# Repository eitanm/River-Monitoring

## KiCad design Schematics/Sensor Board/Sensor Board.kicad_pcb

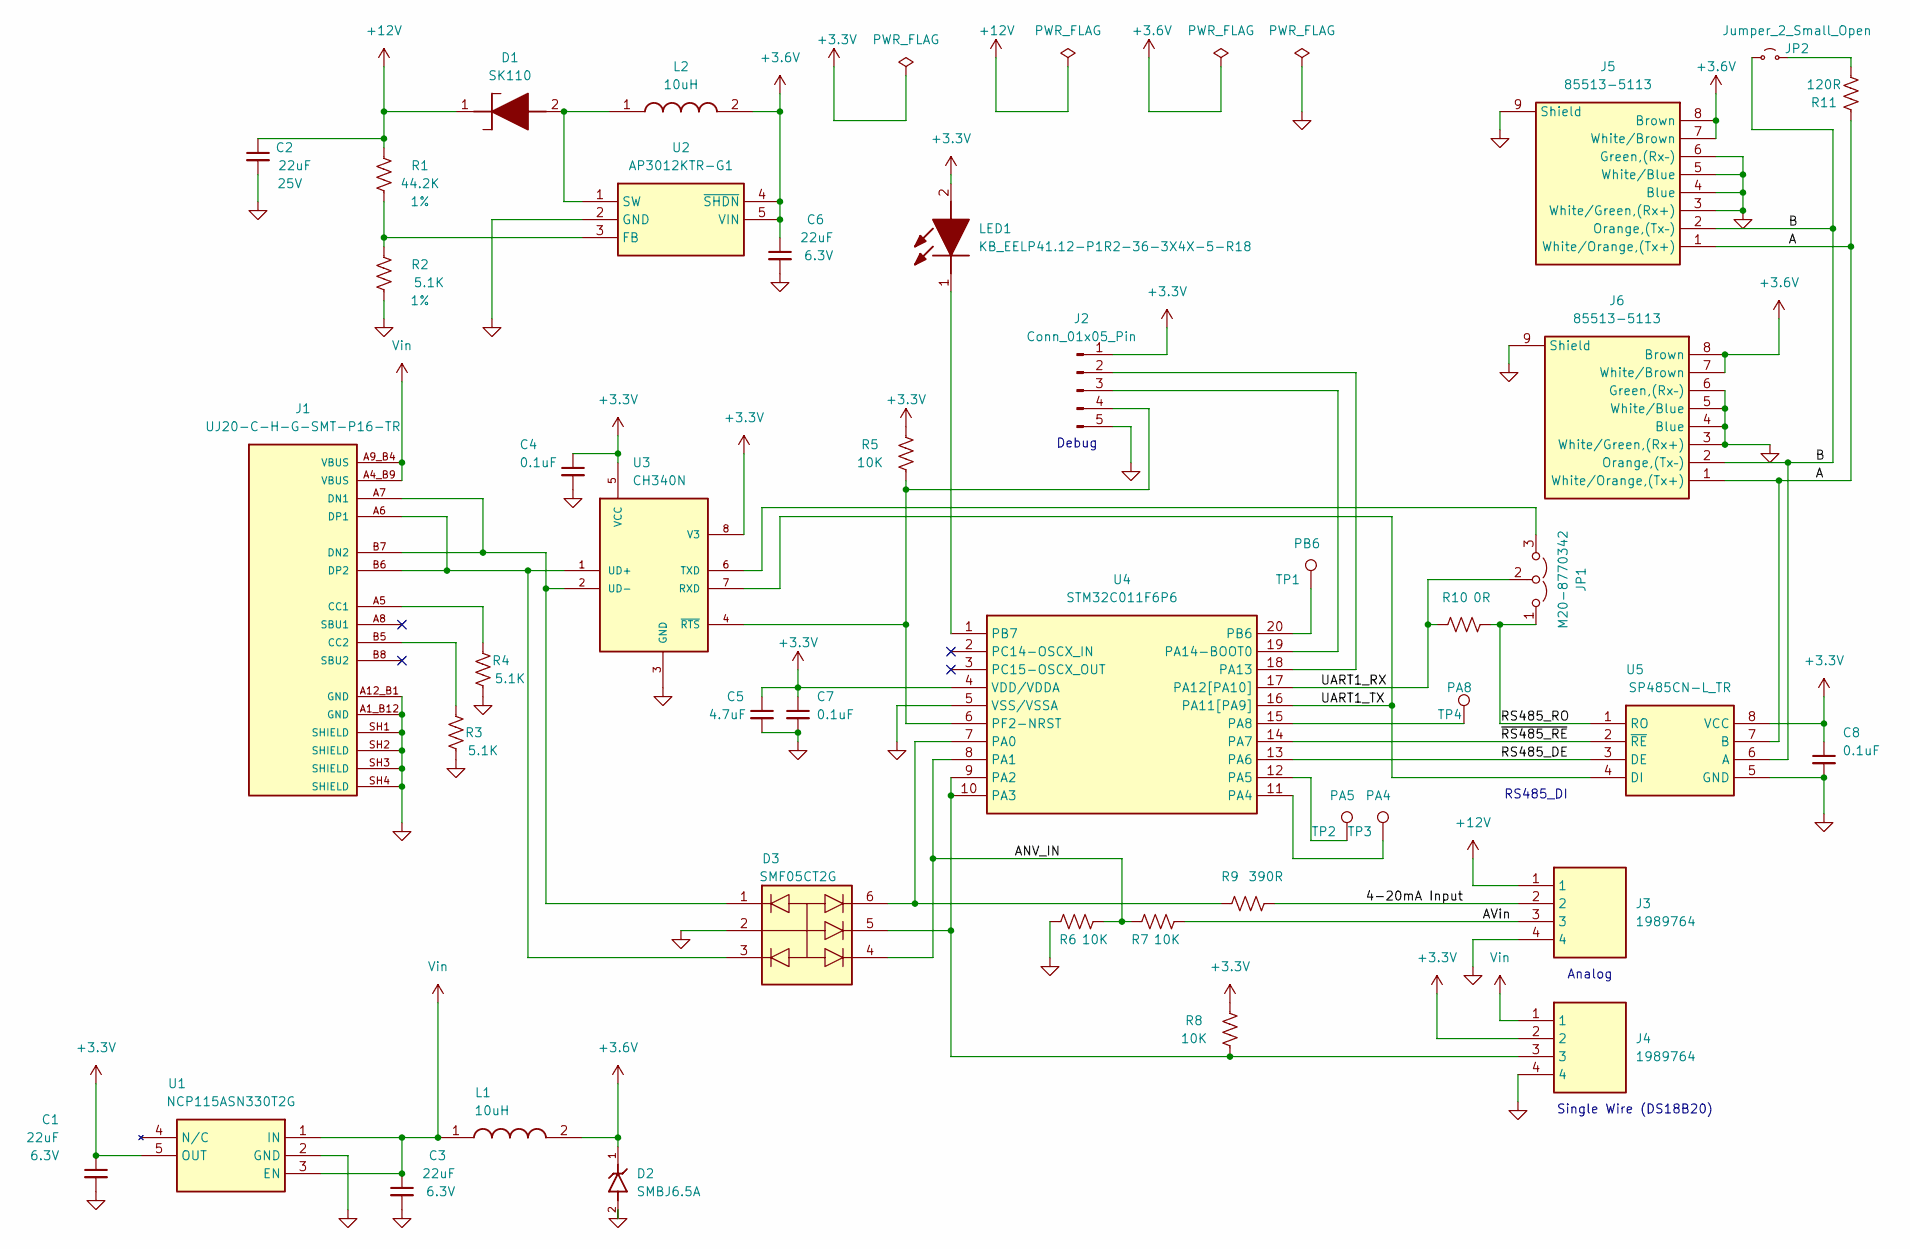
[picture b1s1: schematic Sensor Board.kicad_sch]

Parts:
C1, C3, C6: 22uF; C_0603_1608Metric; Voltage 6.3V; Tolerance 20%
C2: 22uF; C_0805_2012Metric_Pad1.18x1.45mm_HandSolder; Voltage 25V; Tolerance 20%
C4, C7, C8: 0.1uF; C_0603_1608Metric; Voltage 25V; Tolerance 20%
C5: 4.7uF; C_0603_1608Metric; Voltage 25V; Tolerance 20%
D1: SK110; DIOM5027X250N; Mouser Part Number 637-SK110
D2: SMBJ6.5A; D_SMB_Handsoldering; PARTREV JC.07/04/25 v4
D3: SMF05CT2G; Mouser Part Number 863-SMF05CT2G
J1: UJ20-C-H-G-SMT-P16-TR; SAMESKY_UJ20-C-H-G-SMT-P16-TR; PARTREV 1.0
J2: Conn_01x05_Pin; PinHeader_1x05_P2.54mm_Vertical
J3, J4: 1989764; Mouser Part Number 651-1989764
J5, J6: 85513-5113; 855135113; Mouser Part Number 538-85513-5113
JP1: M20-8770342; PinHeader_1x03_P2.54mm_Vertical
JP2: Jumper_2_Small_Open; PinHeader_1x02_P2.54mm_Vertical
L1, L2: 10uH; INDC2012X105N; Mouser Part Number 810-MLZ2012N100LT000
LED1: KB_EELP41.12-P1R2-36-3X4X-5-R18; KBEELP4112P1R2363X4X5R18; Mouser Part Number 720-P4112P1R2363X4X5
R1: 44.2K; R_0603_1608Metric
R2, R3, R4: 5.1K; R_0603_1608Metric
R5, R6, R7, R8: 10K; R_0603_1608Metric
R9: 390R; R_0603_1608Metric
R10: 0R; R_0603_1608Metric
R11: 120R; R_0603_1608Metric
TP1: PB6; TestPoint_THTPad_D1.5mm_Drill0.7mm
TP2: PA5; TestPoint_THTPad_D1.5mm_Drill0.7mm
TP3: PA4; TestPoint_THTPad_D1.5mm_Drill0.7mm
TP4: PA8; TestPoint_THTPad_D1.5mm_Drill0.7mm
U1: NCP115ASN330T2G; SOT95P275X110-5N; Mouser Part Number 863-NCP115ASN330T2G
U2: AP3012KTR-G1; SOT95P282X145-5N; Mouser Part Number 621-AP3012KTR-G1
U3: CH340N; SOIC127P600X175-8N; PARTREV V3C
U4: STM32C011F6P6; SOP65P640X120-20N; Mouser Part Number 511-STM32C011F6P6
U5: SP485CN-L_TR; SOIC127P600X175-8N; Mouser Part Number 701-SP485CN-L/TR

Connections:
+3.3V: C1.1, C4.1, C5.1, C7.1, C8.1, J2.1, J4.2, LED1.2 (A), R5.2, R8.2, U1.5 (OUT), U3.5 (VCC), U3.8 (V3), U4.4 (VDD/VDDA), U5.8 (VCC)
+3.6V: C6.1, D2.1, J5.7 (White/Brown), J5.8 (Brown), J6.7 (White/Brown), J6.8 (Brown), L1.2, L2.2, U2.4 (~SHDN), U2.5 (VIN)
+12V: C2.1, D1.1 (K), J3.1, R1.2
/4-20mA Input: J3.2, R9.1
/A: J5.1 (White/Orange,(Tx+)), J6.1 (White/Orange,(Tx+)), R11.2, U5.7 (B)
/ANV_IN: D3.4 (CATHODE_3), R6.1, R7.2, U4.8 (PA1)
/AVin: J3.3, R7.1
/B: J5.2 (Orange,(Tx–)), J6.2 (Orange,(Tx–)), JP2.1 (A), U5.6 (A)
/RS485_DE: U4.13 (PA6), U5.3 (DE)
/RS485_RO: JP1.1 (A), R10.1, U5.1 (RO)
/UART1_RX: JP1.2 (C), R10.2, U4.17 (PA12[PA10])
/UART1_TX: U3.7 (RXD), U4.16 (PA11[PA9]), U5.4 (DI)
/~RS485_RE: U4.14 (PA7), U5.2 (~RE)
GND: C1.2, C2.2, C3.2, C4.2, C5.2, C6.2, C7.2, C8.2, D2.2, D3.2 (ANODE), J1.A1_B12 (GND), J1.A12_B1 (GND), J1.SH1 (SHIELD), J1.SH2 (SHIELD), J1.SH3 (SHIELD), J1.SH4 (SHIELD), J2.5, J3.4, J4.4, J5.3 (White/Green,(Rx+)), J5.4 (Blue), J5.5 (White/Blue), J5.6 (Green,(Rx–)), J5.9 (Shield), J6.3 (White/Green,(Rx+)), J6.4 (Blue), J6.5 (White/Blue), J6.6 (Green,(Rx–)), J6.9 (Shield), R2.1, R3.1, R4.1, R6.2, U1.2 (GND), U2.2 (GND), U3.3 (GND), U4.5 (VSS/VSSA), U5.5 (GND)
unnamed: D1.2 (A), L2.1, U2.1 (SW)
unnamed: D3.1 (CATHODE_1), J1.A7 (DN1), J1.B7 (DN2), U3.2 (UD-)
unnamed: D3.3 (CATHODE_2), J1.A6 (DP1), J1.B6 (DP2), U3.1 (UD+)
unnamed: D3.5 (CATHODE_4), J4.3, R8.1, U4.9 (PA2), U4.10 (PA3)
unnamed: D3.6 (CATHODE_5), R9.2, U4.7 (PA0)
unnamed: J1.A5 (CC1), R4.2
unnamed: J1.B5 (CC2), R3.2
unnamed: J2.2, U4.18 (PA13)
unnamed: J2.3, U4.19 (PA14-BOOT0)
unnamed: J2.4, R5.1, U3.4 (~RTS), U4.6 (PF2-NRST)
unnamed: JP1.3 (B), U3.6 (TXD)
unnamed: JP2.2 (B), R11.1
unnamed: LED1.1 (K), U4.1 (PB7)
unnamed: R1.1, R2.2, U2.3 (FB)
unnamed: TP3.1 (1_1), U4.11 (PA4)
unnamed: TP2.1 (1_1), U4.12 (PA5)
unnamed: TP4.1 (1_1), U4.15 (PA8)
unnamed: TP1.1 (1_1), U4.20 (PB6)
Vin: C3.1, J1.A4_B9 (VBUS), J1.A9_B4 (VBUS), J4.1, L1.1, U1.1 (IN), U1.3 (EN)

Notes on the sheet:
Analog
Single Wire (DS18B20)
RS485_DI
Debug

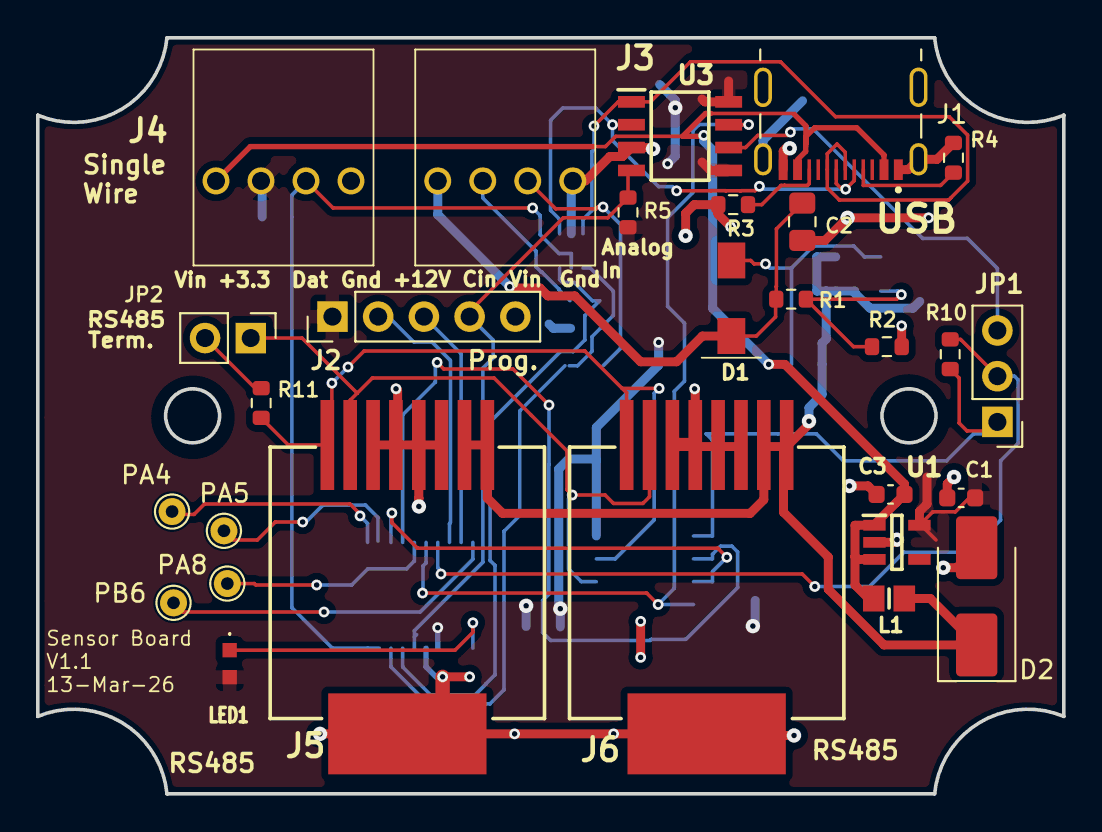
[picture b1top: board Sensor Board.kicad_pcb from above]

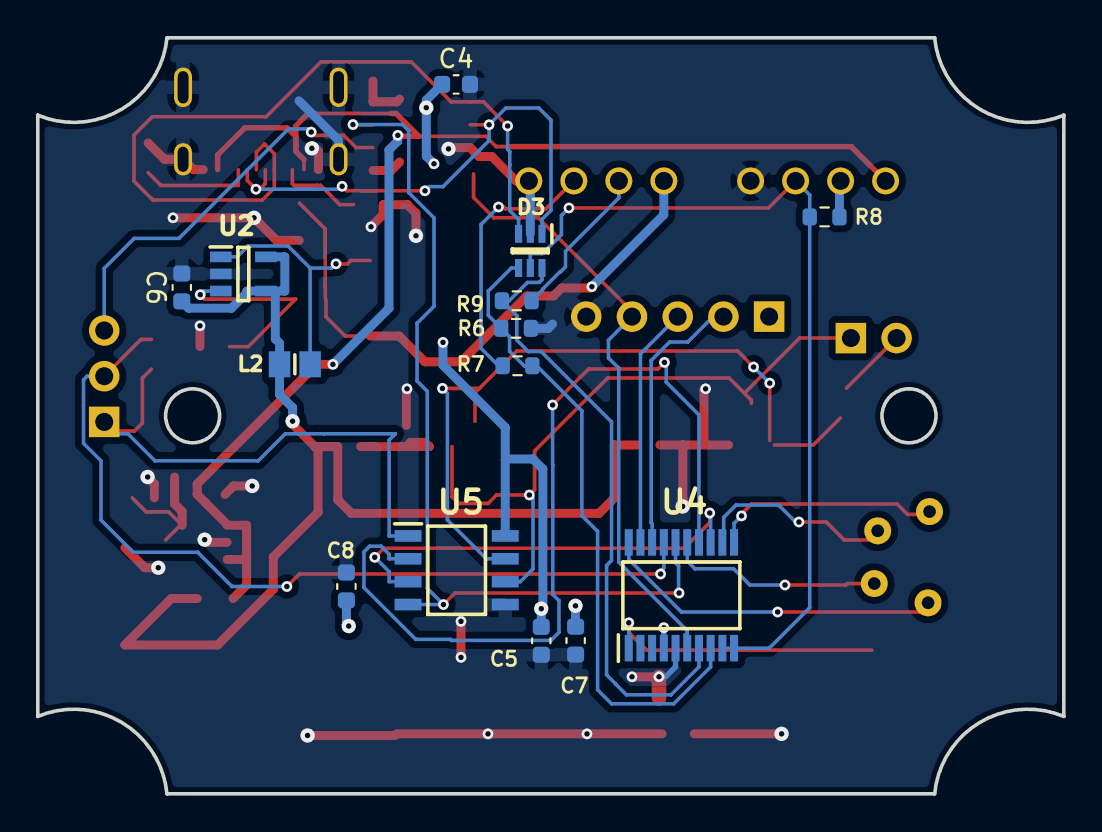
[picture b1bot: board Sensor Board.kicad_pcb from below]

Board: 2 copper layers, 57.0 x 42.0 mm, 42 parts (14 on the bottom side), 33 nets.

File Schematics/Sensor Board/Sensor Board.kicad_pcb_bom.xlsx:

Designator | Quantity | Value | Footprint | Package | MPN | DNP | Mount_Type | Description | PROD_ID | Voltage | Tolerance | Height | Mouser Part Number | Mouser Price/Stock | Manufacturer_Name | MF | MAXIMUM_PACKAGE_HEIGHT | CREATOR | Price | Check_prices | STANDARD | PARTREV | SnapEDA_Link | MP | Description_1 | Availability | MANUFACTURER | Manufacturer | Current | Presision
C1, C3, C6 | 3 | 22uF | C_0603_1608Metric |  |  |  | smt | Unpolarized capacitor | CAP-14464 | 6.3V | 0.2
C2 | 1 | 22uF | C_0805_2012Metric_Pad1.18x1.45mm_HandSolder |  |  |  | smt | Unpolarized capacitor | CAP-14464 | 25V | 0.2
C4, C7, C8 | 3 | 0.1uF | C_0603_1608Metric |  |  |  | smt | Unpolarized capacitor | CAP-00810 | 25V | 0.2
C5 | 1 | 4.7uF | C_0603_1608Metric |  |  |  | smt | Unpolarized capacitor | CAP-00810 | 25V | 0.2
D1 | 1 | SK110 | DIOM5027X250N |  | SK110 |  | smt | Schottky Diodes & Rectifiers Schottky, SMA, 100V, 1A |  |  |  | 2.5 | 637-SK110 | https://www.mouser.co.uk/ProductDetail/Diotec-Semiconductor/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 | Diotec
D2 | 1 | SMBJ6.5A | D_SMB_Handsoldering | DO-214 Littelfuse |  |  | smt |  |  |  |  |  |  |  |  | Littelfuse | 2.61 | ASHISH | None | https://www.snapeda.com/parts/SMBJ6.5A/Littelfuse/view-part/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 | IPC-7351B | JC.07/04/25 v4 | https://www.snapeda.com/parts/SMBJ6.5A/Littelfuse/view-part/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 | SMBJ6.5A | TVS Diode, 600W, 6.5V, -65 to 150 Operating Temp, Surface Mount, SMBJ Series | 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 | In Stock | Littelfuse
D3 | 1 | SMF05CT2G | SMF05CT2G |  | SMF05CT2G |  | smt | Protects up to 5 Lines in a Single SC-88 Package; Peak Power Dissipation - 100W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 |  |  |  | 1.1000000000000001 | 863-SMF05CT2G | https://www.mouser.co.uk/ProductDetail/onsemi/SMF05CT2G?qs=x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 | onsemi
J1 | 1 | UJ20-C-H-G-SMT-P16-TR | SAMESKY_UJ20-C-H-G-SMT-P16-TR | Package |  |  | tht | USB Type C Connector |  |  |  |  |  |  |  | Same Sky | 3.36mm |  | None | https://www.snapeda.com/parts/UJ20-C-H-G-SMT-P16-TR/Same+Sky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 | Manufacturer Recommendations | 1 | https://www.snapeda.com/parts/UJ20-C-H-G-SMT-P16-TR/Same+Sky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 | UJ20-C-H-G-SMT-P16-TR | USB-C (USB TYPE-C) USB 2.0 Receptacle Connector 24 (16+8 Dummy) Position Surfac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 | In Stock | Same Sky | Same Sky
J2 | 1 | Conn_01x05_Pin | PinHeader_1x05_P2.54mm_Vertical |  |  |  | tht | Generic connector, single row, 01x05, script generated
J3, J4, J5, J6 | 4 | 1989764 | 1989764 |  | 1989764 |  | tht | PCB terminal block, nominal current: 2 A, rated voltage (III/2): 250 V, nominal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 |  |  |  | 13.1 | 651-1989764 | https://www.mouser.co.uk/ProductDetail/Phoenix-Contact/19897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 | Phoenix Contact
JP2 | 1 | Jumper_2_Small_Open | PinHeader_1x02_P2.54mm_Vertical |  |  |  | tht | Jumper, 2-pole, small symbol, open
L1, L2 | 2 | 10uH | INDC2012X105N |  | MLZ2012N100LT000 |  | smt | MLZ Series Inductors for Decoupling Circuits Multilayer Ferrite |  |  |  | 1.05 | 810-MLZ2012N100LT000 | https://www.mouser.co.uk/ProductDetail/TDK/MLZ2012N100LT000?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 | TDK |  |  |  |  |  |  |  |  |  |  |  |  | TDK | 500mA
LED1 | 1 | KB_EELP41.12-P1R2-36-3X4X-5-R18 | KBEELP4112P1R2363X4X5R18 |  | KB EELP41.12-P1R2-36-3X4X-5-R18 |  | smt | LED, InGaN on Sapphire, Blue, SMD, 0603 [1608 Metric], 5 mA, 2.75 V, 474 nm |  |  |  | 0.5 | 720-P4112P1R2363X4X5 | https://www.mouser.co.uk/ProductDetail/ams-OSRAM/KB-EELP41.1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 | ams OSRAM
R1 | 1 | 44.2 | R_0603_1608Metric |  |  |  | smt | Resistor, US symbol |  |  |  |  |  |  |  |  |  |  |  |  |  |  |  |  |  |  |  |  |  | 0.01
R10 | 1 | 0R | R_0603_1608Metric |  |  |  | smt | Resistor, US symbol |  |  |  |  |  |  |  |  |  |  |  |  |  |  |  |  |  |  |  |  |  | 0.01
R11 | 1 | 470R | R_0603_1608Metric |  |  |  | smt | Resistor, US symbol |  |  |  |  |  |  |  |  |  |  |  |  |  |  |  |  |  |  |  |  |  | 0.01
R2, R3, R4 | 3 | 5.1K | R_0603_1608Metric |  |  |  | smt | Resistor, US symbol |  |  |  |  |  |  |  |  |  |  |  |  |  |  |  |  |  |  |  |  |  | 0.01
R5, R6, R7, R8 | 4 | 10K | R_0603_1608Metric |  |  |  | smt | Resistor, US symbol |  |  |  |  |  |  |  |  |  |  |  |  |  |  |  |  |  |  |  |  |  | 0.01
R9 | 1 | 390R | R_0603_1608Metric |  |  |  | smt | Resistor, US symbol |  |  |  |  |  |  |  |  |  |  |  |  |  |  |  |  |  |  |  |  |  | 0.01
U1 | 1 | NCP115ASN330T2G | SOT95P275X110-5N |  | NCP115ASN330T2G |  | smt | Operating Input Voltage Range: 1.7 V to 5.5 V; Low Dropout: 250 mV Typical at 3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 |  |  |  | 1.1000000000000001 | 863-NCP115ASN330T2G | https://www.mouser.co.uk/ProductDetail/onsemi/NCP115ASN330T2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 | onsemi |  |  |  |  |  |  |  |  |  |  |  |  | onsemi
U2 | 1 | AP3012KTR-G1 | SOT95P282X145-5N |  | AP3012KTR-G1 |  | smt | Boost Switching Regulator IC Positive Adjustable 1.25V 1 Output 500mA (Switch) 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 |  |  |  | 1.45 | 621-AP3012KTR-G1 | https://www.mouser.co.uk/ProductDetail/Diodes-Incorporated/A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 | Diodes Incorporated
U3 | 1 | CH340N | SOIC127P600X175-8N | Package |  |  | smt | USB to Serial Port Chip |  |  |  |  |  |  |  | WCH | 1.6mm |  | None | https://www.snapeda.com/parts/CH340N/WCH/view-part/?ref=eda | IPC 7351B | V3C | https://www.snapeda.com/parts/CH340N/WCH/view-part/?ref=snap |  |  |  | WCH
U4 | 1 | STM32C011F6P6 | SOP65P640X120-20N |  | STM32C011F6P6 |  | smt | Mainstream Arm Cortex-M0+ MCU with 32 Kbytes of Flash memory, 6 Kbytes RAM, 48 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 |  |  |  | 1.2 | 511-STM32C011F6P6 | https://www.mouser.co.uk/ProductDetail/STMicroelectronics/ST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 | STMicroelectronics
U5 | 1 | SP485CN-L_TR | SOIC127P600X175-8N |  | SP485CN-L/TR |  | smt | RS-485 Interface IC Low Pwr Half-Duplex RS-485 |  |  |  | 1.75 | 701-SP485CN-L/TR | https://www.mouser.co.uk/ProductDetail/MaxLinear/SP485CN-L-T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 | MaxLinear, Inc.

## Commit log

2026-03-12 Add project title to README
2026-03-14 Layout complete of the two PCBs
2026-03-14 Final release 1.1
